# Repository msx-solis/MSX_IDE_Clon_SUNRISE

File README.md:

# MSX-IDE SUNRISE Clon.
Repositorio de ficheros necesarios para la configuración del dispositivo y particionado del disco, sistema operativo, programación del firmware, etc.

Añado copia de los nuevos diseños PCB con ciertas mejoras.

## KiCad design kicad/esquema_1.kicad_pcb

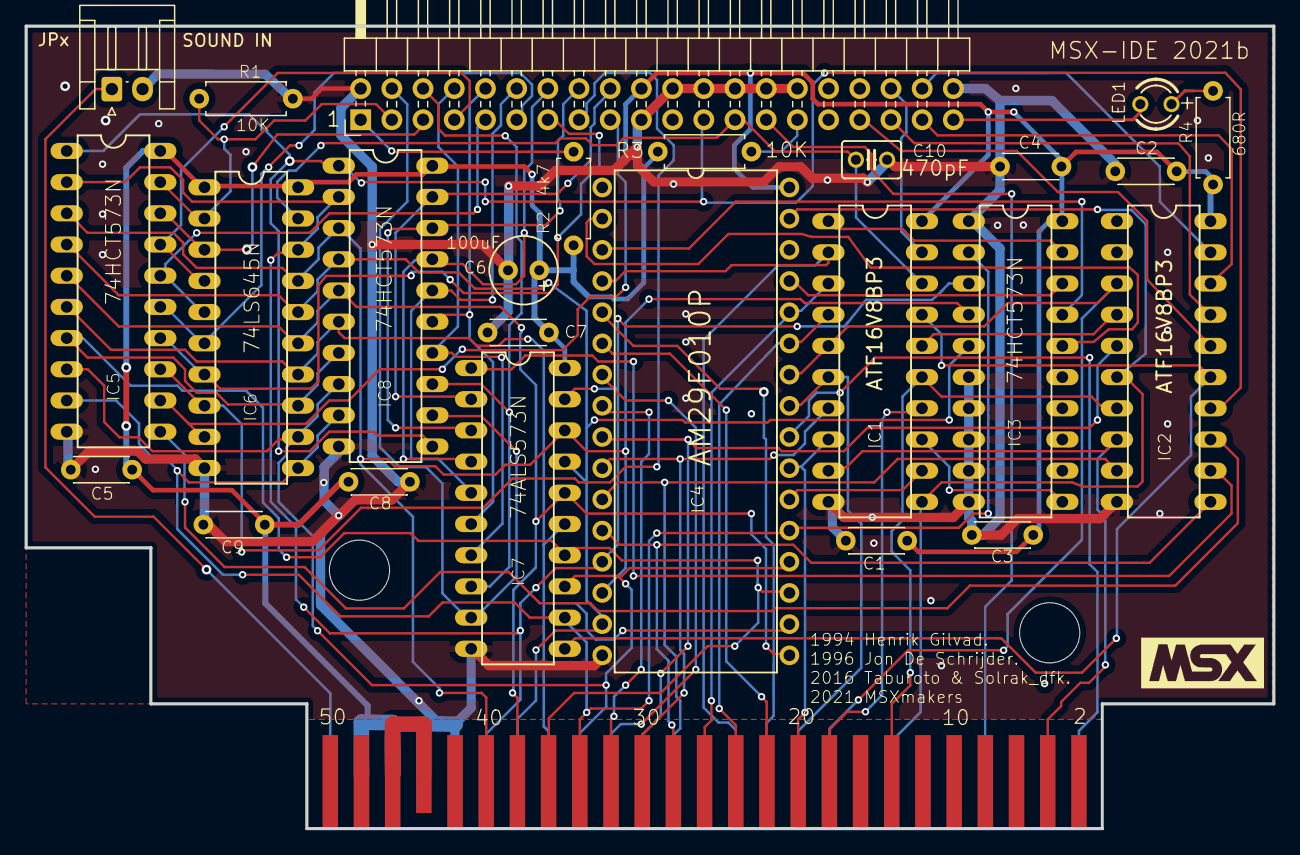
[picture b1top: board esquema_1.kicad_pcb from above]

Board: 2 copper layers, 101.6 x 65.3 mm, 29 parts (1 on the bottom side), 60 nets.

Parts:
C1, C2, C3, C4, C5, C7, C8, C9: 100nF; C_Disc_D4.3mm_W1.9mm_P5.00mm
C6: 100uF; E2,5-6
C10: 470pF; C025-030X050
CON1: CARTRIDGE_MSX_KONAMI_XL; CARTRIDGE_MSX_XL
IC1, IC2: ATF16V8BP3; DIL20
IC3, IC5, IC8: 74HCT573N; DIL20
IC4: AM29F010P; DIL32-3
IC6: 74LS645N; DIL20
IC7: 74ALS573N; DIL20
JPx: SOUND IN; JST_EH_S2B-EH_1x02_P2.50mm_Horizontal
LED1: +; LED3MM
R1, R3: 10K; R_Axial_DIN0207_L6.3mm_D2.5mm_P7.62mm_Horizontal
R2: 4k7; R_Axial_DIN0207_L6.3mm_D2.5mm_P7.62mm_Horizontal
R4: 680R; R_Axial_DIN0207_L6.3mm_D2.5mm_P7.62mm_Horizontal
SV1: PinHeader_2x20_P2.54mm_Horizontal
U$1: SOLRAK_10MM_BOT
U$2: TESLA_10MM_TOP
U$3: MSX_10MM_TOP

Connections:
+5V: C1.1, C2.1, C3.1, C4.1, C5.1, C6.+, C7.1, C8.1, C9.1, IC1.20, IC2.20, IC3.20, IC4.32, IC5.20, IC6.1, IC6.20, IC7.20, IC8.20, R2.2, R3.2, R4.2, SV1.20
//ACTIVE: LED1.K, SV1.39
//FLASH_EN: IC1.12, IC4.22
//IDE_CS0: IC2.18, SV1.37
//IDE_CS1: IC2.19, SV1.38
//IOR: C10.1, IC1.18, IC6.19, SV1.25
//IOW: IC2.14, IC5.1, IC8.1, IC8.11, SV1.23
//RD: IC1.15, IC2.7
//SLTSL: IC1.9, IC2.8
//WR: IC1.11, IC2.6, IC4.31
/A0: IC2.11, IC4.12
/A1: IC2.9, IC4.11
/A2: IC1.7, IC4.10
/A3: IC2.5, IC4.9
/A8: IC1.4, IC4.27
/A9: IC1.5, IC2.3, IC4.26
/A10: IC1.8, IC4.23
/A11: IC1.6, IC4.25
/A12: IC1.2, IC4.4
/A13: IC1.3, IC4.28
/D0: IC3.2, IC4.21, IC5.9, IC6.11, IC7.12, IC8.9
/D1: IC4.20, IC5.8, IC6.12, IC7.13, IC8.8
/D2: IC4.19, IC5.7, IC6.13, IC7.14, IC8.7
/D3: IC4.18, IC5.6, IC6.14, IC7.15, IC8.6
/D4: IC4.17, IC5.5, IC6.15, IC7.16, IC8.5
/D5: IC3.5, IC4.15, IC5.4, IC6.16, IC7.17, IC8.4
/D6: IC3.4, IC4.14, IC5.3, IC6.17, IC7.18, IC8.3
/D7: IC3.3, IC4.13, IC5.2, IC6.18, IC7.19, IC8.2
/DA0: IC2.17, SV1.35
/DA1: IC2.16, SV1.33
/DA2: IC1.19, SV1.36
/DD0: IC5.12, IC6.9, SV1.17
/DD1: IC5.13, IC6.8, SV1.15
/DD2: IC5.14, IC6.7, SV1.13
/DD3: IC5.15, IC6.6, SV1.11
/DD4: IC5.16, IC6.5, SV1.9
/DD5: IC5.17, IC6.4, SV1.7
/DD6: IC5.18, IC6.3, SV1.5
/DD7: IC5.19, IC6.2, R1.1, SV1.3
/DD8: IC7.9, IC8.12, SV1.4
/DD9: IC7.8, IC8.13, SV1.6
/DD10: IC7.7, IC8.14, SV1.8
/DD11: IC7.6, IC8.15, SV1.10
/DD12: IC7.5, IC8.16, SV1.12
/DD13: IC7.4, IC8.17, SV1.14
/DD14: IC7.3, IC8.18, SV1.16
/DD15: IC7.2, IC8.19, SV1.18
/MA: IC1.1, IC3.19
/MA14: IC3.18, IC4.29
/MA15: IC3.17, IC4.3
/MA16: IC3.16, IC4.2
/NET00003: IC2.13, IC5.11
GND: C1.2, C2.2, C3.2, C4.2, C5.2, C6.-, C7.2, C8.2, C9.2, C10.2, IC1.10, IC2.10, IC3.1, IC3.6, IC3.7, IC3.8, IC3.9, IC3.10, IC4.16, IC5.10, IC6.10, IC7.10, IC8.10, R1.2, SV1.2, SV1.19, SV1.22, SV1.24, SV1.26, SV1.28, SV1.30, SV1.40
unnamed: IC1.13, IC3.11
unnamed: IC1.16, IC2.4
unnamed: IC1.17, IC2.15, IC7.11
unnamed: IC2.12, IC7.1
unnamed: LED1.A, R4.1
unnamed: R2.1, SV1.1
unnamed: R3.1, SV1.29
